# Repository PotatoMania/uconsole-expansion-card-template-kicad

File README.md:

# A Template for uConsole Expansion Card

I'm now generously releasing a simple KiCAD template for customizing uConsole expansion cards. This original work was for a custom expansion card which ceased production.

This is not a standard KiCAD template but rather a project skeleton.

- PCB contains 2 layers, and the thickness is 1 mm.
- The manufacturing was done by JLCPCB.
- The board outline was drawn/traced with FreeCAD.

Do not move the footprints of speakers or mini PCIe connector.

Use at your own risk. The data is not guaranteed to be accurate.

This project is licensed under [Creative Commons BY-SA 4.0](https://creativecommons.org/licenses/by-sa/4.0/)

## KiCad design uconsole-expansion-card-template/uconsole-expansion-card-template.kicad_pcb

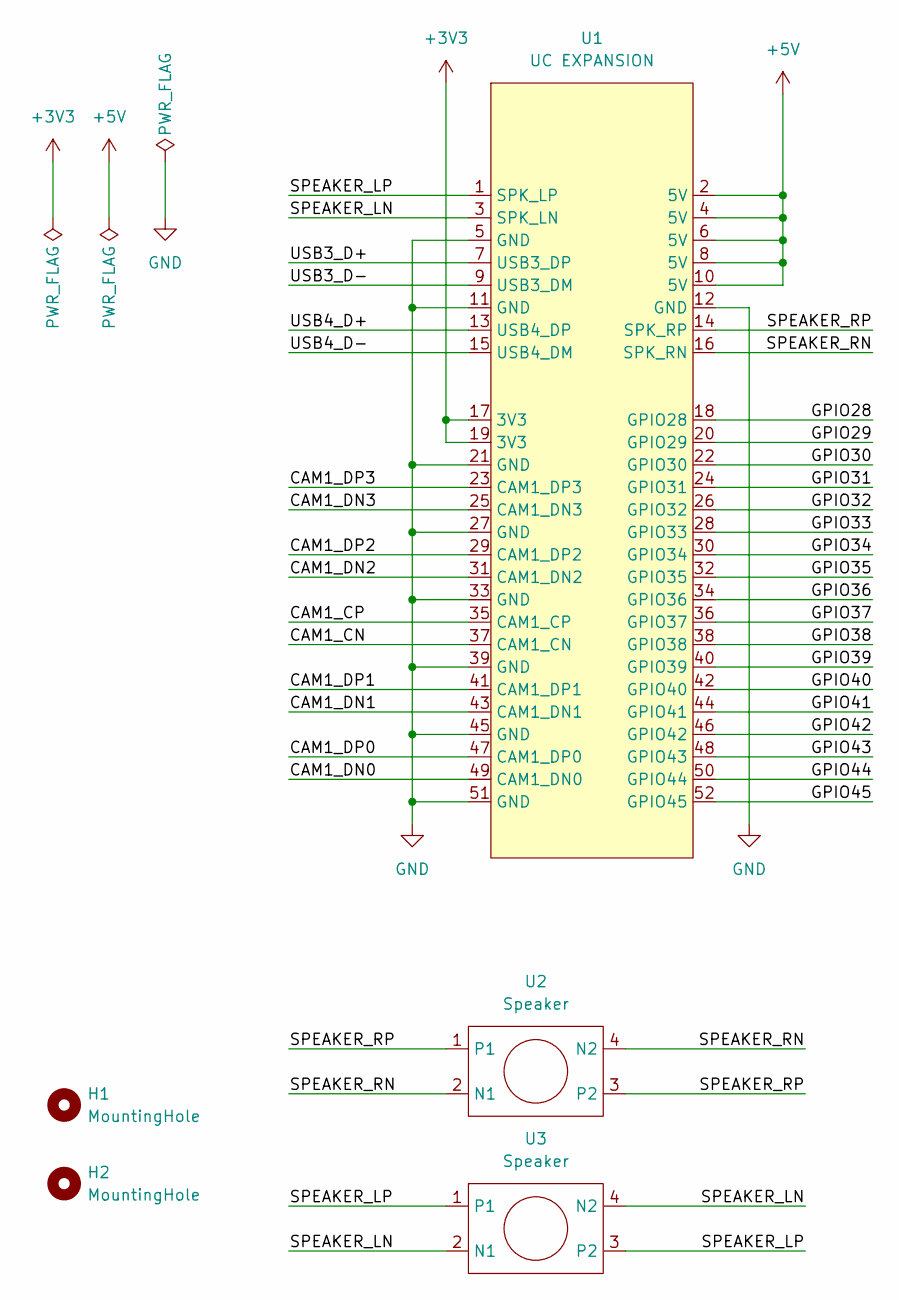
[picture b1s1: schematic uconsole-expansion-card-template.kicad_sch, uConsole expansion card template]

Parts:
H1, H2: MountingHole; MountingHole_5mm
U1: UC EXPANSION; edge-minipcie
U2, U3: Speaker; speaker pads

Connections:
+3V3: U1.17 (3V3), U1.19 (3V3)
+5V: U1.2 (5V), U1.4 (5V), U1.6 (5V), U1.8 (5V), U1.10 (5V)
/CAM1_CN: U1.37 (CAM1_CN)
/CAM1_CP: U1.35 (CAM1_CP)
/CAM1_DN0: U1.49 (CAM1_DN0)
/CAM1_DN1: U1.43 (CAM1_DN1)
/CAM1_DN2: U1.31 (CAM1_DN2)
/CAM1_DN3: U1.25 (CAM1_DN3)
/CAM1_DP0: U1.47 (CAM1_DP0)
/CAM1_DP1: U1.41 (CAM1_DP1)
/CAM1_DP2: U1.29 (CAM1_DP2)
/CAM1_DP3: U1.23 (CAM1_DP3)
/GPIO28: U1.18 (GPIO28)
/GPIO29: U1.20 (GPIO29)
/GPIO30: U1.22 (GPIO30)
/GPIO31: U1.24 (GPIO31)
/GPIO32: U1.26 (GPIO32)
/GPIO33: U1.28 (GPIO33)
/GPIO34: U1.30 (GPIO34)
/GPIO35: U1.32 (GPIO35)
/GPIO36: U1.34 (GPIO36)
/GPIO37: U1.36 (GPIO37)
/GPIO38: U1.38 (GPIO38)
/GPIO39: U1.40 (GPIO39)
/GPIO40: U1.42 (GPIO40)
/GPIO41: U1.44 (GPIO41)
/GPIO42: U1.46 (GPIO42)
/GPIO43: U1.48 (GPIO43)
/GPIO44: U1.50 (GPIO44)
/GPIO45: U1.52 (GPIO45)
/SPEAKER_LN: U1.3 (SPK_LN), U3.2 (N1), U3.4 (N2)
/SPEAKER_LP: U1.1 (SPK_LP), U3.1, U3.3 (P2)
/SPEAKER_RN: U1.16 (SPK_RN), U2.2 (N1), U2.4 (N2)
/SPEAKER_RP: U1.14 (SPK_RP), U2.1, U2.3 (P2)
/USB3_D+: U1.7 (USB3_DP)
/USB3_D-: U1.9 (USB3_DM)
/USB4_D+: U1.13 (USB4_DP)
/USB4_D-: U1.15 (USB4_DM)
GND: U1.5 (GND), U1.11 (GND), U1.12 (GND), U1.21 (GND), U1.27 (GND), U1.33 (GND), U1.39 (GND), U1.45 (GND), U1.51 (GND)

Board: 2 copper layers, 5 parts (2 on the bottom side), 7 nets, no tracks yet.

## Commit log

2024-07-10 publish a template
2024-07-10 add a readme
2024-07-10 add an experimental funding link
2025-02-11 add board outline dxf, and minor update in README
